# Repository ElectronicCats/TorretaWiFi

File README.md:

# Torreta ESP

El gato vigilante de la torre es un dispositivo open hardware basado en el chip ESP8266 que monitorea el estado de las torretas industriales **Patlite®**, sin modificar el circuito usted puede monitorear el tiempo de encendido y apagado de cada luz que este en la torreta, puede obtener por medio de una red WiFi o exportar sus datos en una microSD para generar despues sus reportes, facil de implementar solo debe ser agregado en uno de los espacios disponibles de la torreta.

#Features
- Tiempo acumulado de paro
- Tiempo de inicio de paro
- Access point con WebServer
- Pagina web local datos de paro y arranque
- Slot de Micro SD para almacenamiento en un archivo
- Bateria recargable 3.7v

## TODO

- Mejora de pagina de home
- Conexión Mesh entre dispositivos
- Connexión Punto a Punto entre dispositivos (P2P)
- Conexión entre dispositivos esclavos y dispositivo maestro

## LICENSING
Electronic Cats invests time and resources providing this open source design, please support Electronic Cats and open-source hardware by purchasing products from Electronic Cats!

Designed by Electronic Cats.

Firmware released under an GNU AGPL v3.0 license. See the LICENSE file for more information.

Hardware released under an CERN Open Hardware Licence v1.2. See the LICENSE_HARDWARE file for more information.

Electronic Cats is a registered trademark, please do not use if you sell these PCBs.

27 December 2017

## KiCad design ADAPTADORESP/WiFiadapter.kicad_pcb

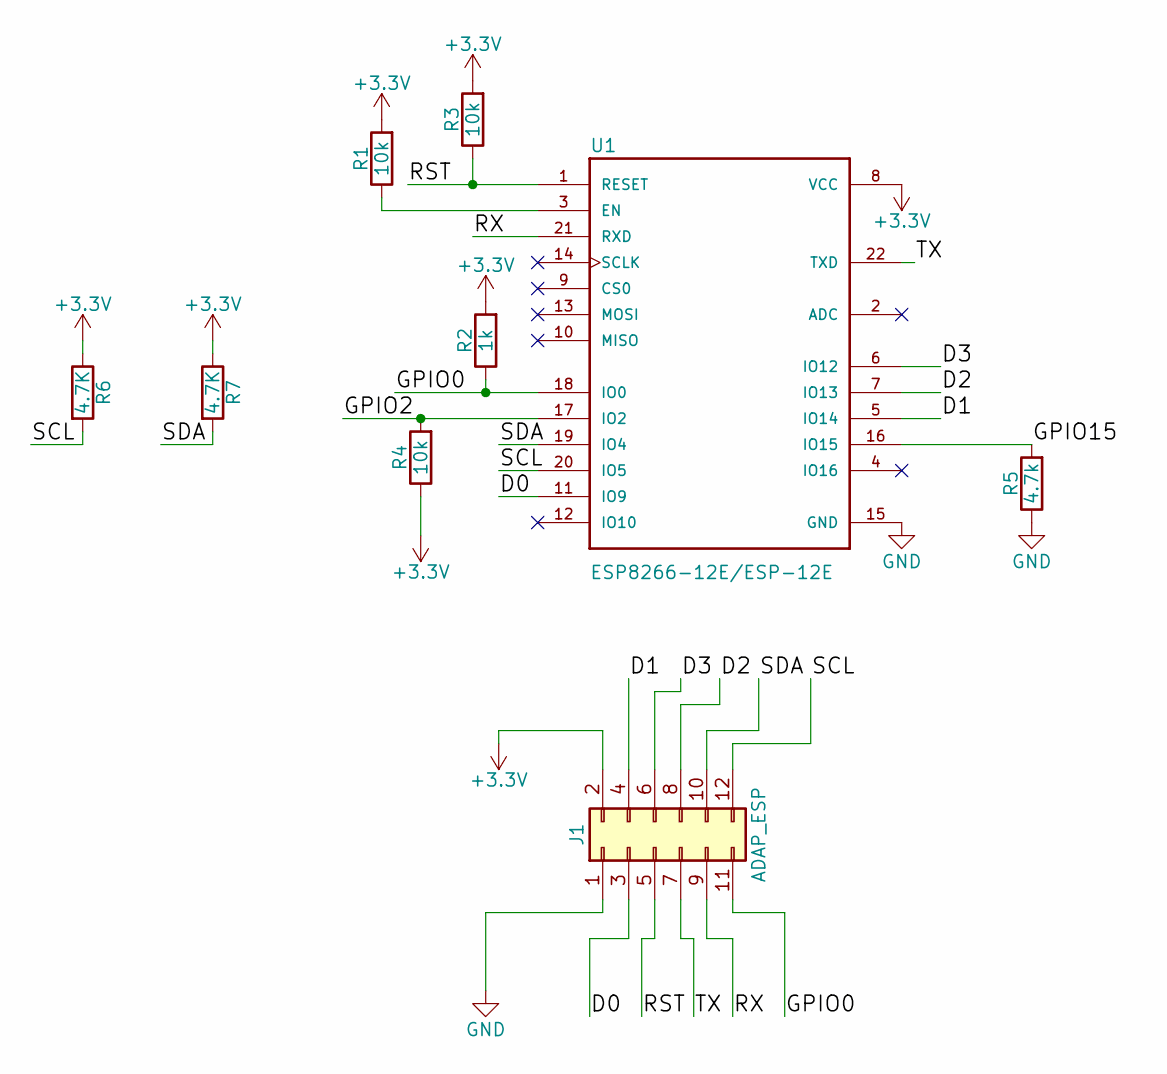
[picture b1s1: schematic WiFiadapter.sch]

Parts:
J1: ADAP_ESP; Pin_Header_Straight_2x06_Pitch2.54mm
R1, R3, R4: 10k; R_0805_HandSoldering
R2: 1k; R_0805_HandSoldering
R5: 4.7k; R_0805_HandSoldering
R6, R7: 4.7K; R_0805_HandSoldering
U1: ESP8266-12E/ESP-12E; XCVR_ESP8266-12E%2fESP-12E

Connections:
+3V3: J1.2, R1.2, R2.2, R3.2, R4.1, R6.1, R7.1, U1.8 (VCC)
/D0: J1.3, U1.11 (IO9)
/D1: J1.4, U1.5 (IO14)
/D2: J1.8, U1.7 (IO13)
/D3: J1.6, U1.6 (IO12)
/GPIO0: J1.11, R2.1, U1.18 (IO0)
/GPIO2: R4.2, U1.17 (IO2)
/GPIO15: R5.2, U1.16 (IO15)
/RST: J1.5, R3.1, U1.1 (RESET)
/RX: J1.9, U1.21 (RXD)
/SCL: J1.12, R6.2, U1.20 (IO5)
/SDA: J1.10, R7.2, U1.19 (IO4)
/TX: J1.7, U1.22 (TXD)
GND: J1.1, R5.1, U1.15 (GND)
unnamed: R1.1, U1.3 (EN)

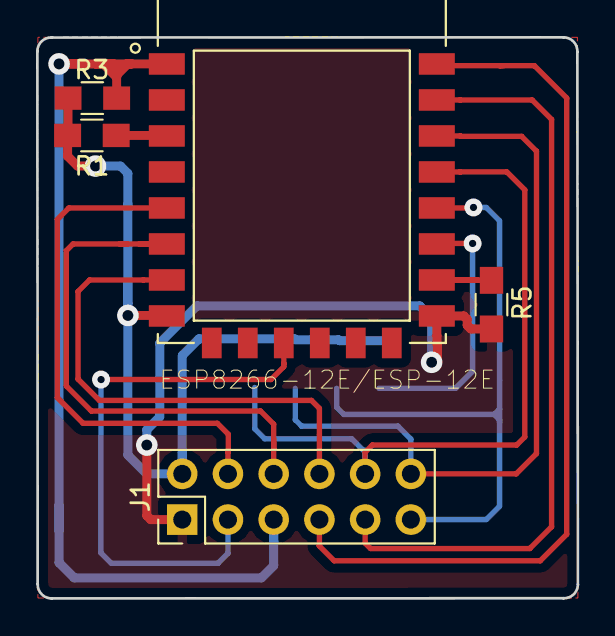
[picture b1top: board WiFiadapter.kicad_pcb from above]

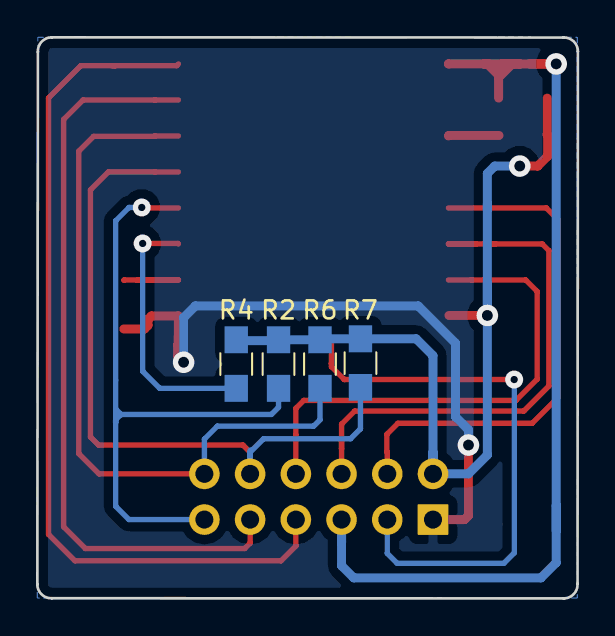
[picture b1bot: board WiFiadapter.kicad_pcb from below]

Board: 2 copper layers, 30.0 x 31.2 mm, 9 parts (4 on the bottom side), 15 nets.

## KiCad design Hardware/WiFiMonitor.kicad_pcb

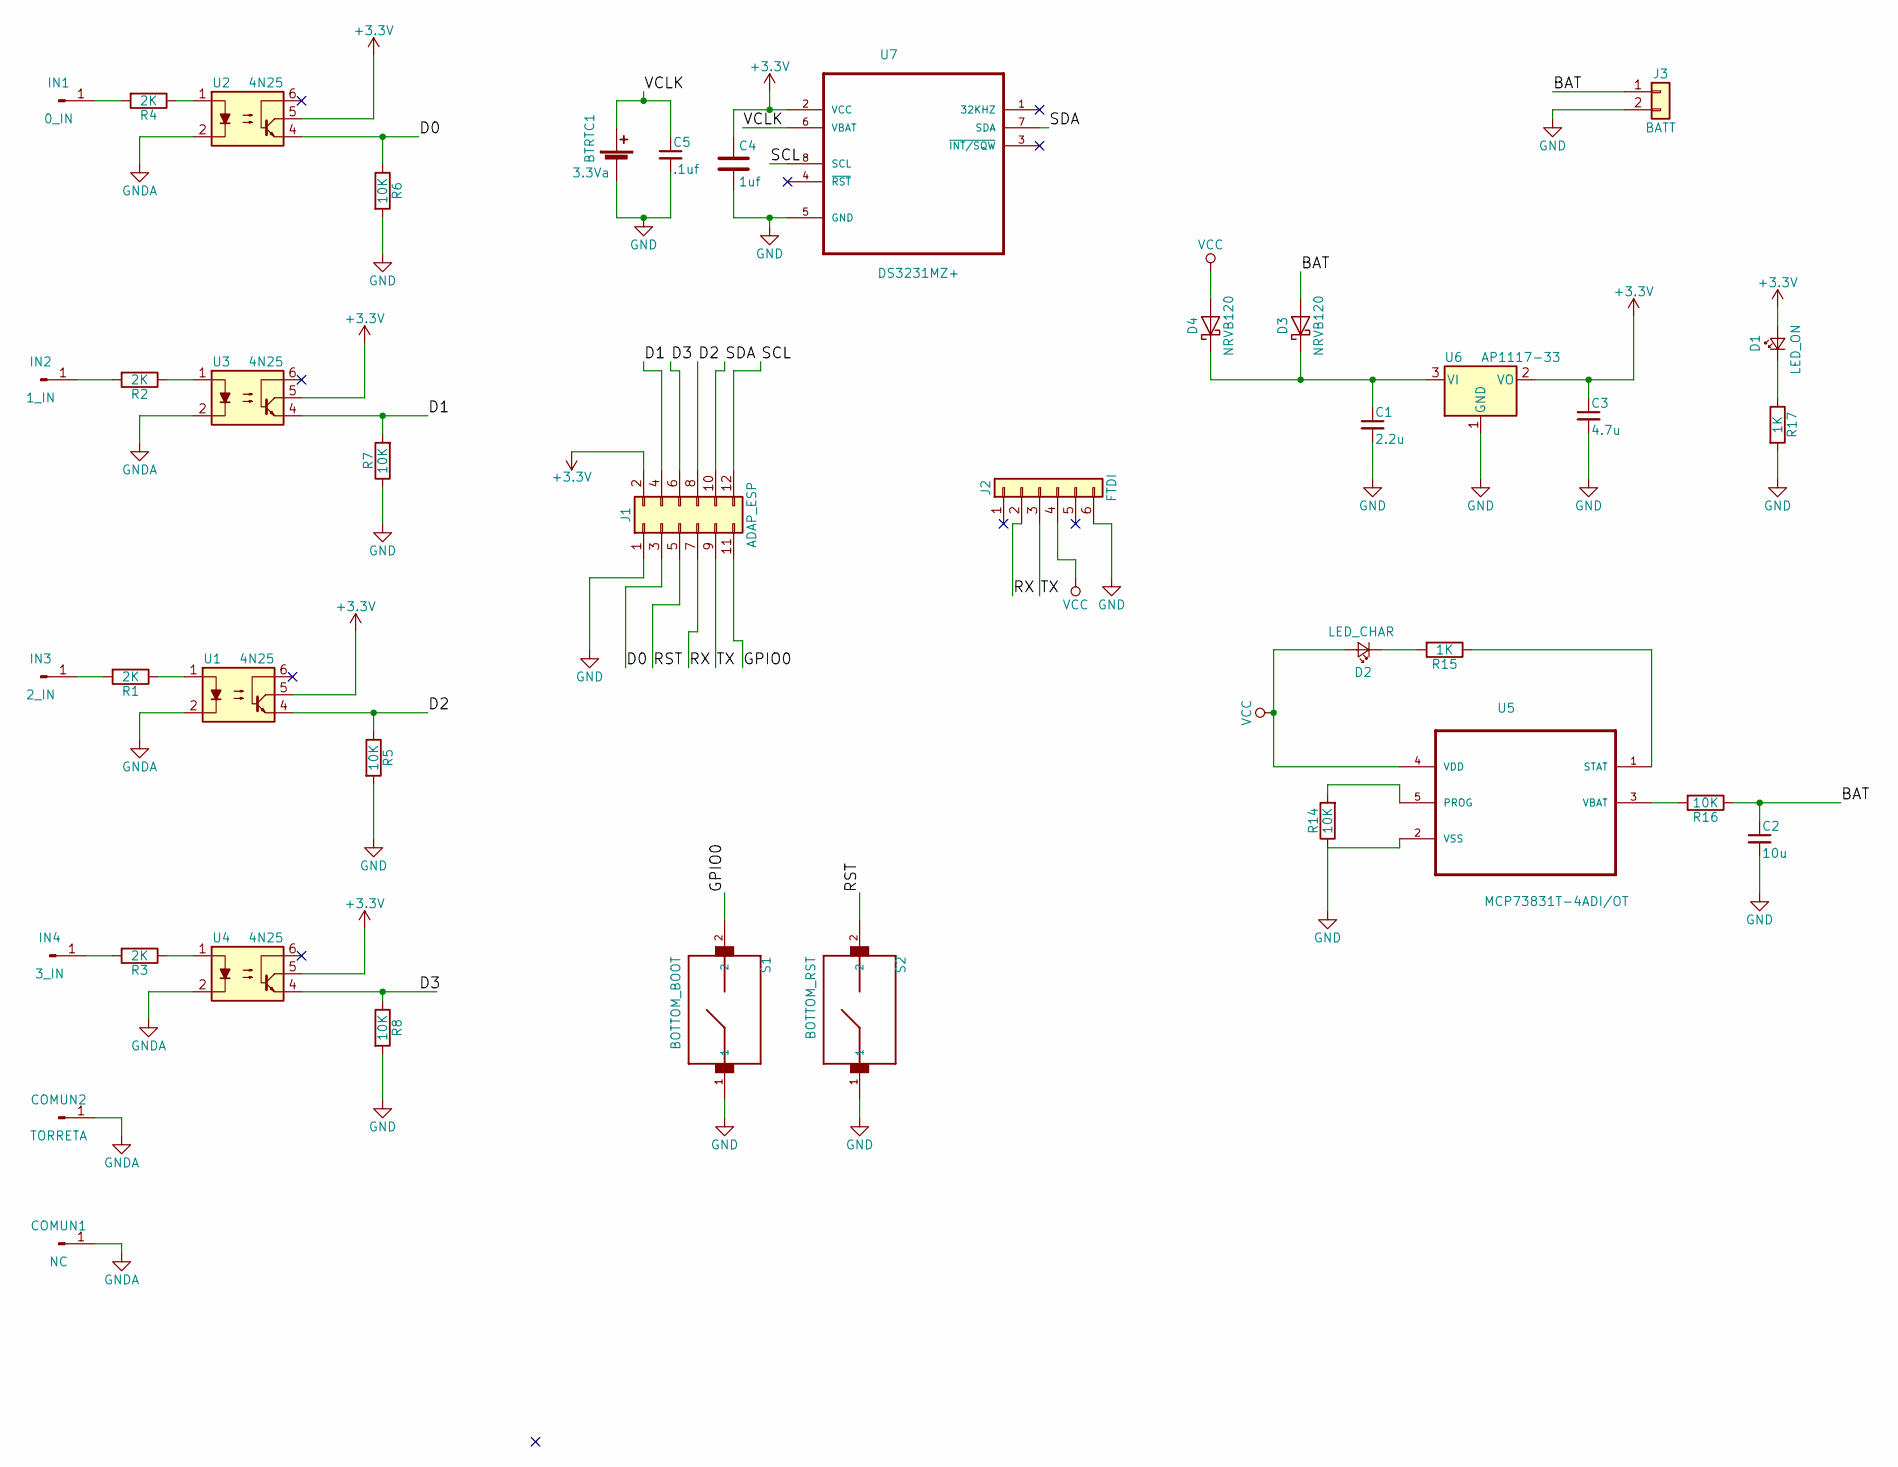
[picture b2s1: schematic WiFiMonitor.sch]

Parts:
BTRTC1: 3.3Va; Keystone_battery_second
C1: 2.2u; C_0805_HandSoldering
C2: 10u; C_0805_HandSoldering
C3: 4.7u; C_0805_HandSoldering
C4: 1uf; C_0805_HandSoldering
C5: .1uf; C_0805_HandSoldering
COMUN1: NC; PAD_5x3mm
COMUN2: TORRETA; PAD_5x3mm
D1: LED_ON; LED_0805_HandSoldering
D2: LED_CHAR; LED_0805_HandSoldering
D3, D4: NRVB120; D_SOD-123
IN1: 0_IN; PAD_5x3mm
IN2: 1_IN; PAD_5x3mm
IN3: 2_IN; PAD_5x3mm
IN4: 3_IN; PAD_5x3mm
J1: ADAP_ESP; Pin_Header_Straight_2x06_Pitch2.54mm
J2: FTDI; Pin_Header_Straight_1x06_Pitch2.54mm
J3: BATT; PINHEAD1-2
R1, R2, R3, R4: 2K; R_0805_HandSoldering
R5, R6, R7, R8, R14, R16: 10K; R_0805_HandSoldering
R15, R17: 1K; R_0805_HandSoldering
S1: BOTTOM_BOOT; SW_B3U-1000P
S2: BOTTOM_RST; SW_B3U-1000P
U1, U2, U3, U4: 4N25; DIP-6_W7.62mm_SMDSocket_SmallPads
U5: MCP73831T-4ADI/OT; SOT95P280X145-5N
U6: AP1117-33; SOT-223-3_TabPin2
U7: DS3231MZ+; SOIC8_150MIL

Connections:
+3V3: C3.1, C4.1, D1.2 (A), J1.2, U1.5, U2.5, U3.5, U4.5, U6.2 (VO), U7.2 (VCC)
/BAT: C2.1, D3.2 (A), J3.1, R16.1, R16.2, U5.3 (VBAT)
/D0: J1.3, R6.1, U2.4
/D1: J1.4, R7.2, U3.4
/D2: J1.8, R5.1, U1.4
/D3: J1.6, R8.1, U4.4
/GPIO0: J1.11, S1.2
/RST: J1.5, S2.2
/RX: J1.7, J2.2
/SCL: J1.12, U7.8 (SCL)
/SDA: J1.10, U7.7 (SDA)
/TX: J1.9, J2.3
/VCLK: BTRTC1.1 (+), C5.1, U7.6 (VBAT)
GND: BTRTC1.2 (-), C1.2, C2.2, C3.2, C4.2, C5.2, J1.1, J2.6, J3.2, R5.2, R6.2, R7.1, R8.2, R14.1, R17.2, S1.1, S2.1, U5.2 (VSS), U6.1 (GND), U7.5 (GND); also elsewhere on the board
GNDA: COMUN1.1, COMUN2.1, U1.2, U2.2, U3.2, U4.2; also elsewhere on the board
unnamed: C1.1, D3.1 (K), D4.1 (K), U6.3 (VI)
unnamed: D1.1 (K), R17.1
unnamed: D2.1 (K), R15.2
unnamed: IN1.1, R4.2
unnamed: IN2.1, R2.2
unnamed: IN3.1, R1.2
unnamed: IN4.1, R3.2
unnamed: R1.1, U1.1
unnamed: R2.1, U3.1
unnamed: R3.1, U4.1
unnamed: R4.1, U2.1
unnamed: R14.2, U5.5 (PROG)
unnamed: R15.1, U5.1 (STAT)
VCC: D2.2 (A), D4.2 (A), J2.4, U5.4 (VDD); also elsewhere on the board

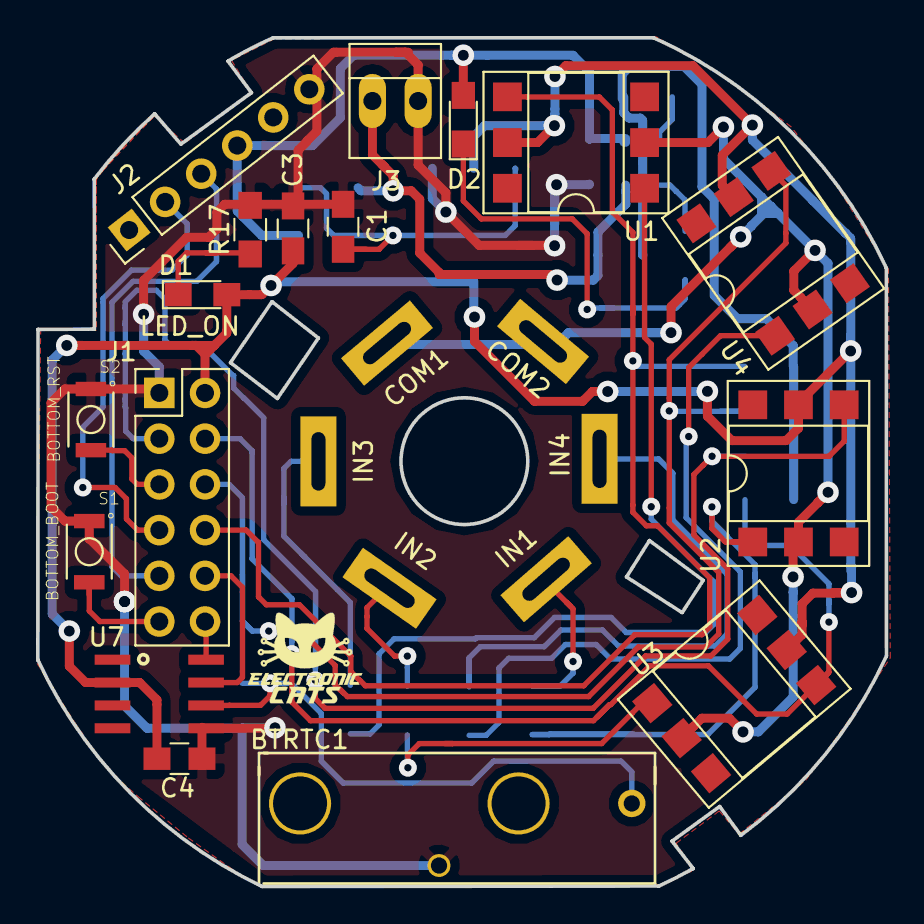
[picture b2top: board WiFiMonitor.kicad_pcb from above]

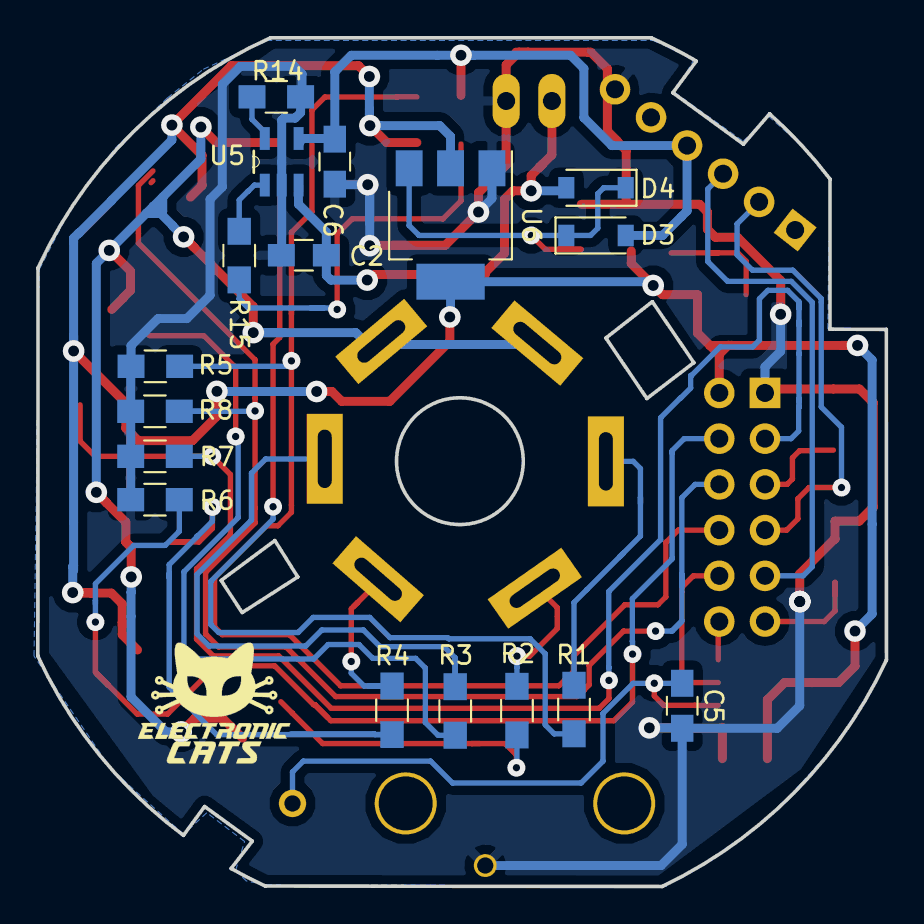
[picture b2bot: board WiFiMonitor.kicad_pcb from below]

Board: 2 copper layers, 47.2 x 47.1 mm, 40 parts (17 on the bottom side), 29 nets.

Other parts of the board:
C6: 4.7U; C_0805_HandSoldering
COM1: NC; PAD_4X2mmTH
COM2: TORRETA; PAD_4X2mmTH

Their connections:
GND: C6.2; also elsewhere on the board
GNDA: COM1.1, COM2.1; also elsewhere on the board
VCC: C6.1; also elsewhere on the board

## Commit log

2017-10-11 versión beta
2017-10-13 Depuración
    Cambio de usurio y contraseña
    Print en serial
    Cambio en lectura de variables
2017-11-13 Reloj RTC
    Inicialización de algoritmo para reloj RTC
2017-11-14 Solucion temporal
2017-11-15 Tiempo de encendido y apagado RTC
    diferencia de tiempo de cambio
    unicamente con entrada D0 (amarillo)
2017-11-27 Libreria "ImpresionDeTiempos"
    en esta libreria se manda el parametro DateTime y regresa la impresion serial del tiempo (hora, minuto y segundo)
2017-12-14 Agregado comentarios
2017-12-25 HTML_SAVEDATA
    Agrege datos en la pagina web y descarga datos en un excel desde el server
2017-12-27 Agregado SD
2017-12-27 Optimizado Serial print en memoria
2017-12-27 BorradolibraryUDP
    wifi
2017-12-27 Agregado esquematico
2017-12-27 TXTTIMEDEAD
    Edicion de formato en el txt e identificacion del tiempo muerto(amarillo)
2017-12-27 Change SD for SPIFF
2017-12-27 Agregado la descarga de archivo
2017-12-28 SPIFFSDATO
    Guarda el historial completo, borrar las horas en apagado del cerial print, agregar descarga en html
2018-01-01 Esch-torreta
    RTC DS3231 8 PINES Y USB-B CON REGULADOR LM 1117 3.3V
2018-01-01 eschematic
    todos los archivos
2018-01-03 Charger
    Agregue el MCP73831 manager y el conector de la pila, tambien se cambio el ESP por el conector acondicionado para el esp.
2018-01-04 Final
    Corregi nombres, y agregue el circuito de programación
2018-01-05 PULL_UP_BOTTON
    RESISTENCIAS CORREGIDAS PULL UP DEL RTC Y CAMBIO DE BOTON
2018-01-05 VCC
    Etiqueta VCC y VCC ESP cambiado por 3.3
2018-01-12 ADAP_MEDIDAS
    Adaptador del ESP8266 para programación. Y modificacion del esquematico placa principal para el adaptador.
2018-01-13 PCBS_Adap_mon
    Correxión del RX y TX del adaptador, PCB monitor doble capa.
2018-01-13 Tracks fix
2018-01-14 PCB_PISTAS
    Reacomodo de pistas
2018-01-17 PADS_TH
    Pads de los voltajes de entradas en Through-Hole y espacio para el tornillo en el centro,
2018-01-17 DS3231
    Prueba del funcionamiento del RTC DS3231
2018-01-18 RTC_capacitor
    Se agrego el capacitor al DS3231 a pcb y esquematico. Movimiento de vista 3D a los conectores, y cambio de pistas.
2018-01-18 Fix vias at the power side, and fix labels
2018-01-19 Fix vias and stuff FTW
2018-01-19 Added logo EC
2018-01-19 Auto stash before merge of "HARDWARER" and "origin/HARDWARER"
    6 PINES FTDI
2018-01-19 Adapter_TXRX
    TX RX change
2018-01-19 Pista_near
    Move
2018-01-19 pads_in
    move
2018-01-19 pads2
    move
2018-01-19 pads3
    move
2018-01-19 pads4
    move
2018-01-19 pcb_adapter
    Redondeo de la placa
2018-01-20 pads4_1
    edge board
2018-01-20 pads4_2
2018-01-20 pads4_21
    move
2018-01-20 pads4_22
    move
2018-01-20 pads4_23
    move
2018-01-23 modificacion_pistas
    reacomodo
2018-01-23 Gerbers
    generar nuevos
2018-01-23 gerberzip
    comprimir
2018-01-29 size_file
    Conocer el espacio libre respecto al tamaño del archivo generado en la memoria flash.
2018-01-30 Access point and generate new historial
2018-02-01 Botton confirm new historial
    Boton de confirmar crear nuevo historial en el servidor
2018-02-03 Access_point
    Sequito el modo station wifi
2018-02-12 CHANGE TX-RX CASE BATTERY RTC AND CAPACITOR RTC
2018-02-12 RTC_saved_data
2018-04-26 update gitignore
2018-04-26 Add receptor firmware
2018-04-27 Station code indicators
2018-04-27 Client code send data string for excel to station
2018-04-27 Station code with label to excel
2018-05-24 Modification save history two states in excel
2018-05-24 Identify manual state and test state
2018-05-24 Add state manual and test
2018-05-24 Add manual mode in server and change lenguage
2018-05-24 Save data when dowload document
2018-05-24 Blink yellow bug test
2018-05-24 Charger
2018-05-31 Clear code, bug Test solutioned.
2018-06-01 Manual only change
2018-06-03 changes charger sch
2018-06-04 Time Actual and time Antes in the states
2018-06-04 Server without manual
2018-06-08 Fix calculation more 24 hours
2018-06-08 Fix 24 hours clean
2018-06-11 Change date day
2018-06-11 Change GPIO16 to GPIO09
2018-06-13 Acumulate time and date test
2018-06-13 Clean test date
2018-06-15 Password change date fix
